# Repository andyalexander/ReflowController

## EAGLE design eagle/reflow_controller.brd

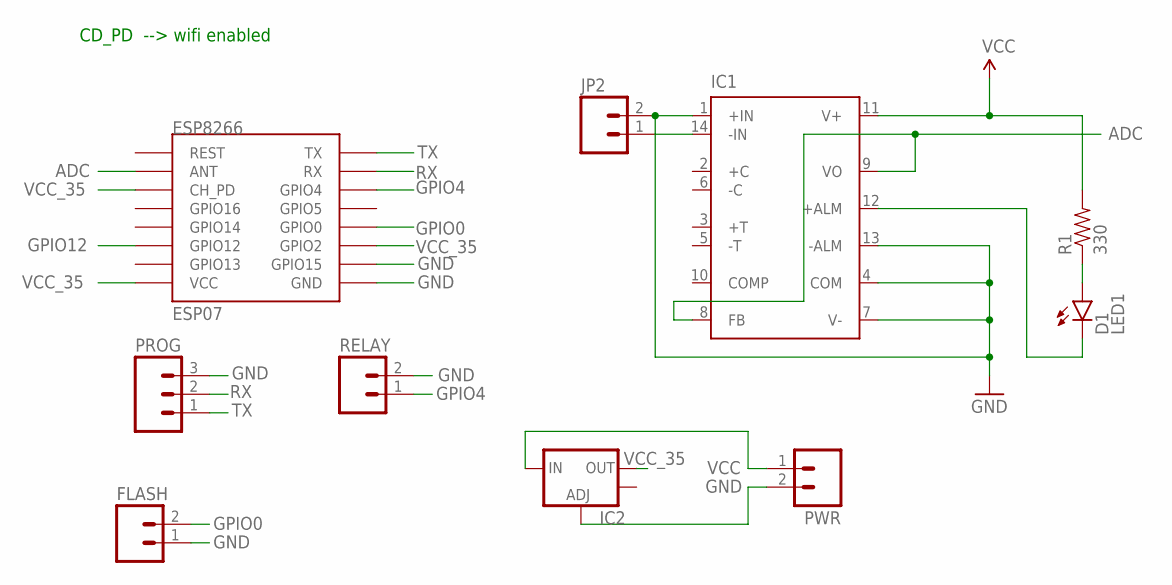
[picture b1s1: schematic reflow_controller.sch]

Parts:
D1: LED1; LED5MM
ESP8266: ESP07
FLASH: M02LOCK; 1X02_LOCK
IC1: AD595; DIL14
IC2: V_REG_LM1117SOT223; SOT223
JP2: M025MM; SCREWTERMINAL-5MM-2
PROG: M03PTH; 1X03
PWR: M02LOCK; 1X02_LOCK
R1: 330; AXIAL-0.3-KIT
RELAY: M02LOCK; 1X02_LOCK

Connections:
ADC: ESP8266.ANT, IC1.8 (FB), IC1.9 (VO)
GND: ESP8266.GND, ESP8266.GPIO15, FLASH.1, IC1.1 (+IN), IC1.4 (COM), IC1.7 (V-), IC1.13 (-ALM), IC2.1 (ADJ), JP2.2, PROG.3, PWR.2, RELAY.2
GPIO0: ESP8266.GPIO0, FLASH.2
GPIO4: ESP8266.GPIO4, RELAY.1
GPIO12: ESP8266.GPIO12
unnamed: D1.A, R1.P$1 (1)
unnamed: IC1.14 (-IN), JP2.1
unnamed: D1.K (C), IC1.12 (+ALM)
RX: ESP8266.RX, PROG.2
TX: ESP8266.TX, PROG.1
VCC: IC1.11 (V+), IC2.3 (IN), PWR.1, R1.P$2 (2)
VCC_35: ESP8266.CH_PD, ESP8266.GPIO2, ESP8266.VCC, IC2.2 (OUT)

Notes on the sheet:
CD_PD --> wifi enabled

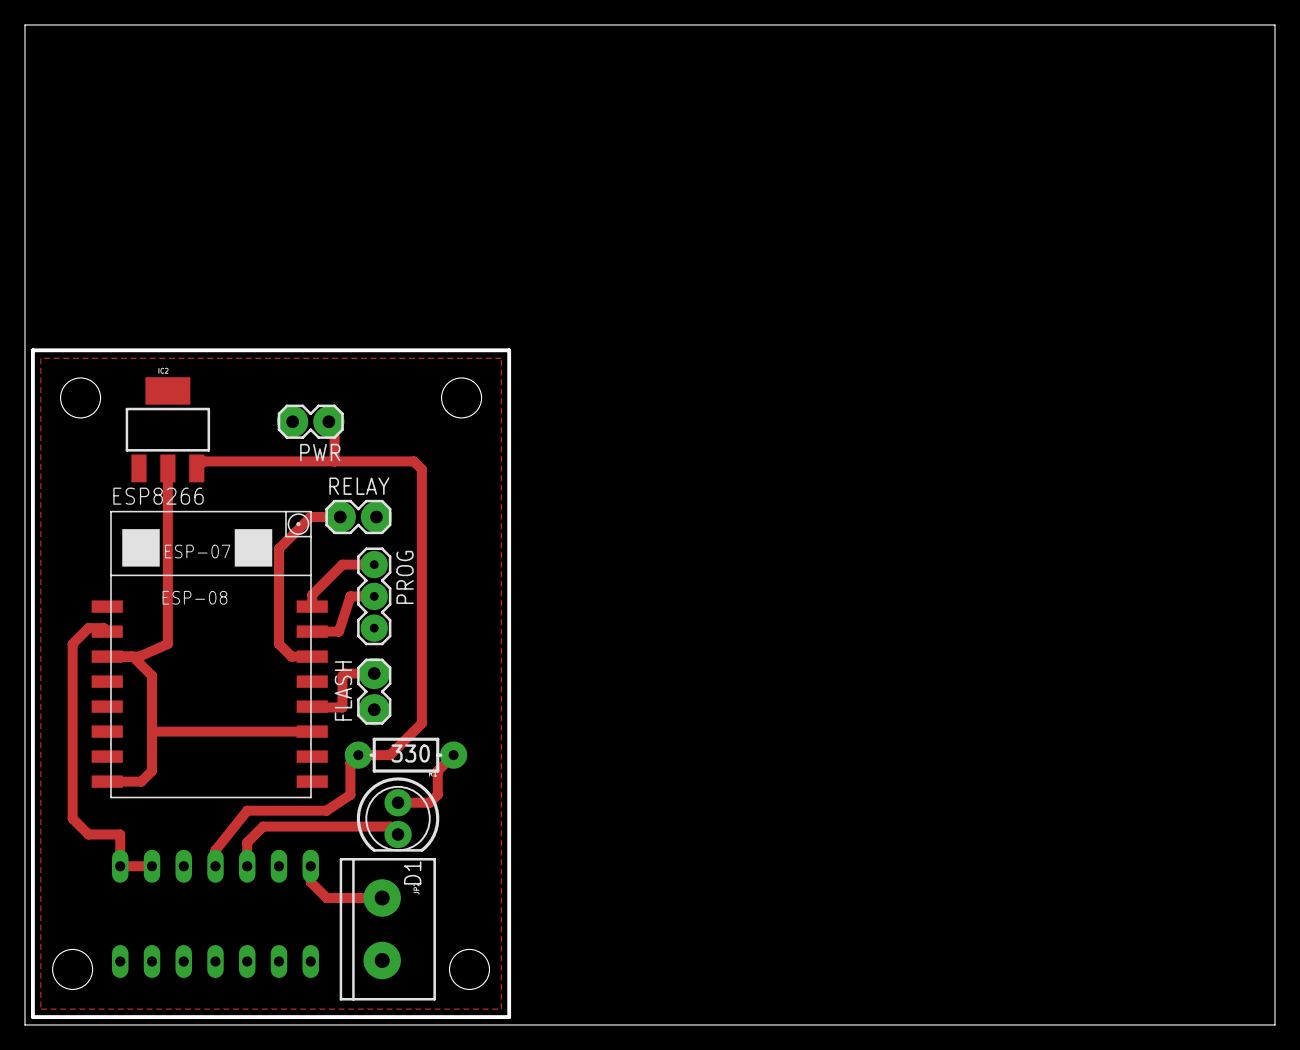
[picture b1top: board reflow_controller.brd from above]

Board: 2 copper layers, 100.0 x 80.0 mm, 10 parts (1 on the bottom side), 11 nets.

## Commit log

2015-08-31 Misc updates
2015-09-12 Fixed gpio numbers
2015-09-12 added eagle files

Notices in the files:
parts and their libraries:
SparkFun-LED: Licensing: Creative Commons ShareAlike 4.0 International - https://creativecommons.org/licenses/by-sa/4.0
